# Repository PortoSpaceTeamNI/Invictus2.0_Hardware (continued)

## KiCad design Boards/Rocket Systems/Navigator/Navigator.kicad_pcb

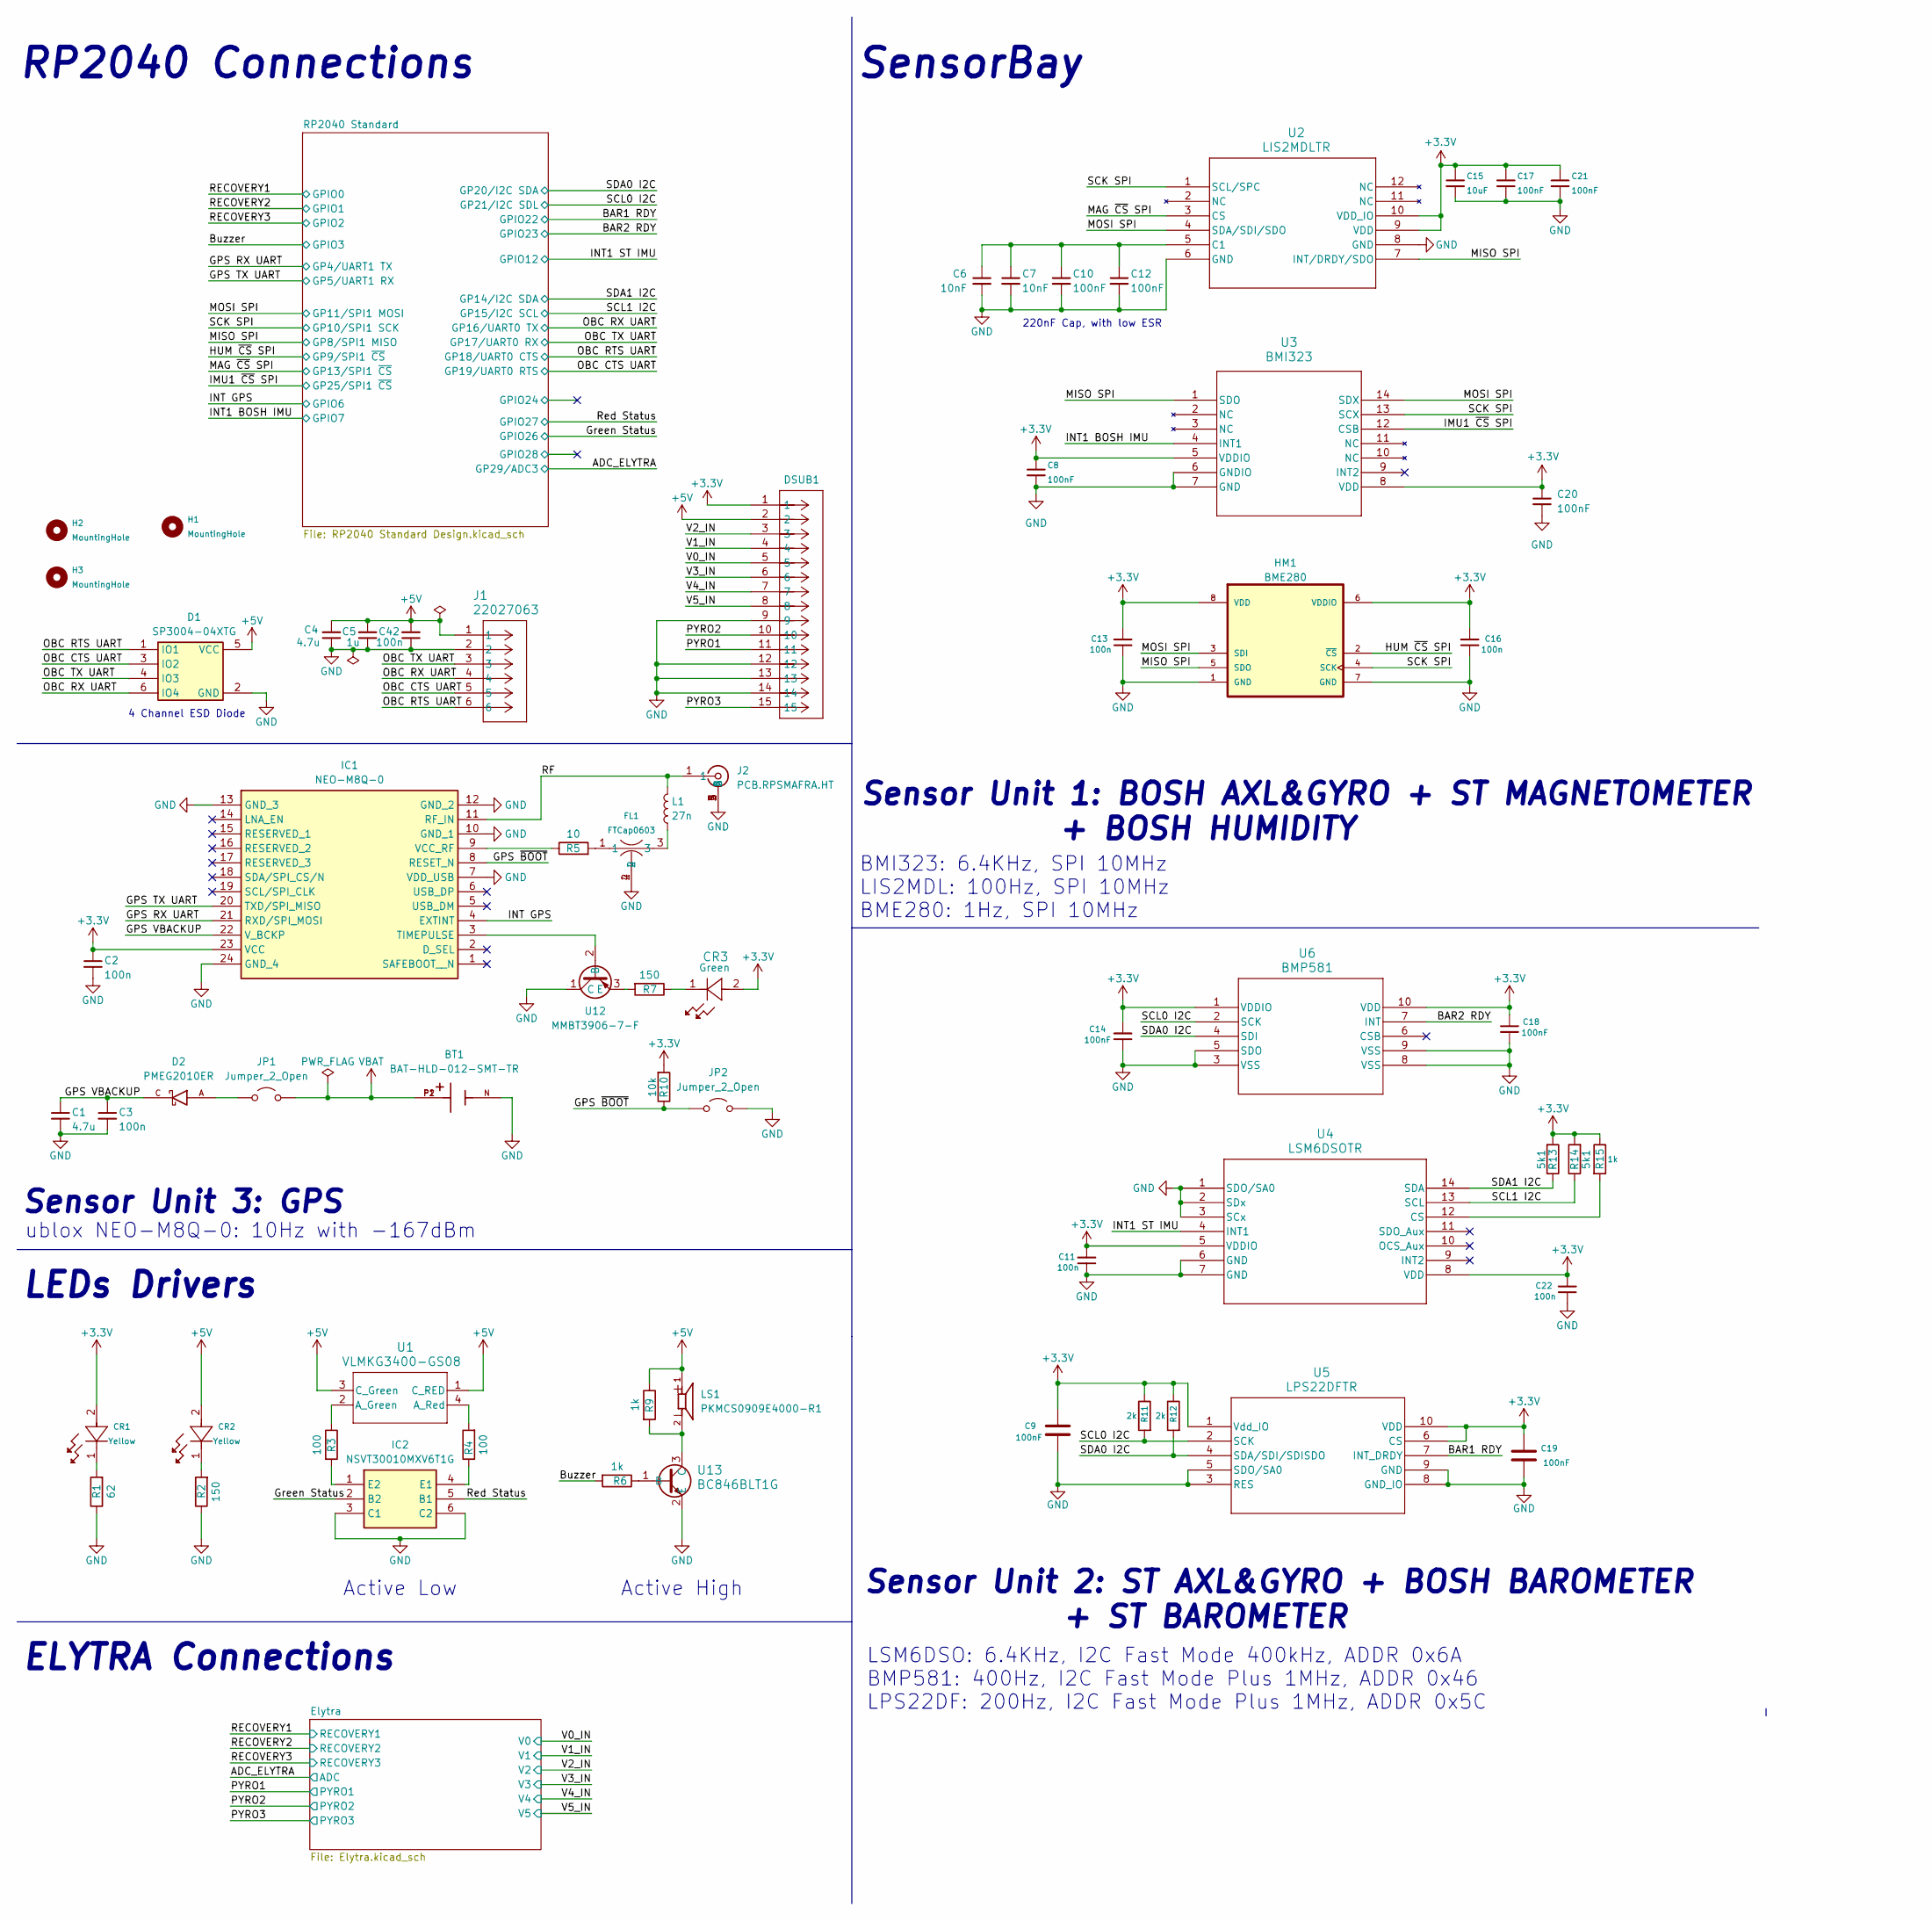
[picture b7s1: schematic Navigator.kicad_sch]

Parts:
BT1: BAT-HLD-012-SMT-TR; BAT_BAT-HLD-012-SMT-TR; PARTREV A
C1, C4: 4.7u; Capacitor_0402
C2, C3, C11, C13, C16, C22, C42: 100n; Capacitor_0402
C5: 1u; Capacitor_0402
C6, C7: 10nF; Capacitor_0402
C8, C9, C10, C12, C14, C17, C18, C19, C20, C21: 100nF; Capacitor_0402
C15: 10uF; Capacitor_0805
CR1, CR2: VLMY1300-GS08; LEDC1608X100N
CR3: VLMC3100-GS08; LED_PLCC_VSMB
D1: SP3004-04XTG; SOT563_LTF; Mouser Part Number 576-SP3004-04XTG
D2: PMEG2010ER; SODFL3517X110N; PARTREV 01
DSUB1: HDL15-SL-B
FL1: FTCap0603; FTCap_0603
H1, H2, H3: MountingHole; MountingHole_3.2mm_M3_ISO7380
HM1: BME280; Mouser Part Number 262-BME280
IC1: NEO-M8Q-0; NEO-M8_UBL; Mouser Part Number 377-NEO-M8Q-0
IC2: NSVT30010MXV6T1G; SOTFL50P160X60-6N; Mouser Part Number 863-NSVT30010MXV6T1G
J1: 22027063; CONN6X1_22027063_MOL
J2: PCB.RPSMAFRA.HT; PCBRPSMAFRAHT; Mouser Part Number 960-PCB.RPSMAFRA.HT
JP1, JP2: Jumper_2_Open; SolderJumper-2_P1.3mm_Open_RoundedPad1.0x1.5mm
L1: 27n; Inductor_0402
LS1: PKMCS0909E4000-R1; SPKR_PKMCS0909E4000-R1; PARTREV May 22, 2020
R1: 62; RES_0603
R2, R7: 150; RES_0603
R3, R4: 100; RES_0603
R5: 10; RES_0402
R6, R9: 1k; RES_0603
R10: 10k; RES_0402
R11, R12: 2k; RES_0402
R13, R14: 5k1; RES_0402
R15: 1k; RES_0402
U1: VLMKG3400-GS08; SMT_00-GS08_VIS
U2: LIS2MDLTR; LGA-12_2X2X1_STM
U3: BMI323; BMI323_BOS
U4: LSM6DSOTR; LGA-14L_2P5X3X0P86_STM
U5: LPS22DFTR; QFN_22DFTR_STM
U6: BMP581; QFN10_BMP581_BOS
U12: MMBT3906-7-F; SOT103P240X110-3N; MPN MMBT3906-7-F
U13: BC846BLT1G; SOT-23_ONS

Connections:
+3.3V: C2.1, C8.1, C9.2, C11.2, C13.2, C14.2, C15.1, C16.2, C17.1, C18.1, C19.2, C20.1, C21.1, C22.2, CR1.2, CR3.2, DSUB1.1, HM1.6 (VDDIO), HM1.8 (VDD), IC1.23 (VCC), R10.2, R11.1, R12.1, R13.2, R14.2, R15.1, U2.9 (VDD), U2.10 (VDD_IO), U3.5 (VDDIO), U3.8 (VDD), U4.5 (VDDIO), U4.8 (VDD), U5.1 (Vdd_IO), U5.6 (CS), U5.10 (VDD), U6.1 (VDDIO), U6.10 (VDD); also elsewhere on the board
+5V: C4.2, C5.2, C42.2, CR2.2, D1.5 (VCC), DSUB1.2, J1.1, LS1.1, R9.1, U1.1 (C_RED), U1.3 (C_Green); also elsewhere on the board
/BAR1 RDY: U5.7 (INT_DRDY); also elsewhere on the board
/BAR2 RDY: U6.7 (INT); also elsewhere on the board
/Buzzer: R6.2; also elsewhere on the board
/GPS RX UART: IC1.21 (RXD/SPI_MOSI); also elsewhere on the board
/GPS TX UART: IC1.20 (TXD/SPI_MISO); also elsewhere on the board
/GPS VBACKUP: C1.1, C3.1, D2.C, IC1.22 (V_BCKP)
/GPS ~BOOT: IC1.8 (RESET_N), JP2.1 (A), R10.1
/Green Status: IC2.2 (B2); also elsewhere on the board
/HUM ~CS SPI: HM1.2 (~CS); also elsewhere on the board
/IMU1 ~CS SPI: U3.12 (CSB); also elsewhere on the board
/INT1 BOSH IMU: U3.4 (INT1); also elsewhere on the board
/INT1 ST IMU: U4.4 (INT1); also elsewhere on the board
/INT GPS: IC1.4 (EXTINT); also elsewhere on the board
/MAG ~CS SPI: U2.3 (CS); also elsewhere on the board
/MISO SPI: HM1.5 (SDO), U2.7 (INT/DRDY/SDO), U3.1 (SDO); also elsewhere on the board
/MOSI SPI: HM1.3 (SDI), U2.4 (SDA/SDI/SDO), U3.14 (SDX); also elsewhere on the board
/OBC CTS UART: D1.3 (IO2), J1.5; also elsewhere on the board
/OBC RTS UART: D1.1 (IO1), J1.6; also elsewhere on the board
/OBC RX UART: D1.6 (IO4), J1.4; also elsewhere on the board
/OBC TX UART: D1.4 (IO3), J1.3; also elsewhere on the board
/PYRO1: DSUB1.11; also elsewhere on the board
/PYRO2: DSUB1.10; also elsewhere on the board
/PYRO3: DSUB1.15; also elsewhere on the board
/RF: IC1.11 (RF_IN), J2.1, L1.2
/Red Status: IC2.5 (B1); also elsewhere on the board
/SCK SPI: HM1.4 (SCK), U2.1 (SCL/SPC), U3.13 (SCX); also elsewhere on the board
/SCL0 I2C: R11.2, U5.2 (SCK), U6.2 (SCK); also elsewhere on the board
/SCL1 I2C: R14.1, U4.13 (SCL); also elsewhere on the board
/SDA0 I2C: R12.2, U5.4 (SDA/SDI/SDISDO), U6.4 (SDI); also elsewhere on the board
/SDA1 I2C: R13.1, U4.14 (SDA); also elsewhere on the board
/V0_IN: DSUB1.5; also elsewhere on the board
/V1_IN: DSUB1.4; also elsewhere on the board
/V2_IN: DSUB1.3; also elsewhere on the board
/V3_IN: DSUB1.6; also elsewhere on the board
/V4_IN: DSUB1.7; also elsewhere on the board
/V5_IN: DSUB1.8; also elsewhere on the board
GND: BT1.N, C1.2, C2.2, C3.2, C4.1, C5.1, C6.2, C7.2, C8.2, C9.1, C10.2, C11.1, C12.2, C13.1, C14.1, C15.2, C16.1, C17.2, C18.2, C19.1, C20.2, C21.2, C22.1, C42.1, D1.2 (GND), DSUB1.9, DSUB1.12, DSUB1.13, DSUB1.14, FL1.2, FL1.4, HM1.1 (GND), HM1.7 (GND), IC1.7 (VDD_USB), IC1.10 (GND_1), IC1.12 (GND_2), IC1.13 (GND_3), IC1.24 (GND_4), IC2.3 (C1), IC2.6 (C2), J1.2, J2.2, J2.3, J2.4, J2.5, JP2.2 (B), R1.1, R2.1, U2.6 (GND), U2.8 (GND), U3.6 (GNDIO), U3.7 (GND), U4.1 (SDO/SA0), U4.2 (SDx), U4.3 (SCx), U4.6 (GND), U4.7 (GND), U5.3 (RES), U5.5 (SDO/SA0), U5.8 (GND_IO), U5.9 (GND), U6.3 (VSS), U6.5 (SDO), U6.8 (VSS), U6.9 (VSS), U12.1 (C), U13.2 (E); also elsewhere on the board
unnamed: CR1.1, R1.2
unnamed: CR2.1, R2.2
unnamed: CR3.1, R7.1
unnamed: FL1.1, R5.2
unnamed: FL1.3, L1.1
unnamed: IC1.3 (TIMEPULSE), U12.2 (B)
unnamed: IC1.9 (VCC_RF), R5.1
unnamed: IC2.4 (E1), R4.1
unnamed: IC2.1 (E2), R3.2
unnamed: D2.A, JP1.1 (A)
unnamed: R3.1, U1.2 (A_Green)
unnamed: R4.2, U1.4 (A_Red)
unnamed: C6.1, C7.1, C10.1, C12.1, U2.5 (C1)
unnamed: R15.2, U4.12 (CS)
unnamed: R7.2, U12.3 (E)
unnamed: R6.1, U13.1 (B)
unnamed: LS1.2, R9.2, U13.3 (C)
VBAT: BT1.P1, BT1.P2, JP1.2 (B)

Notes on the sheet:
BMI323: 6.4KHz, SPI 10MHz LIS2MDL: 100Hz, SPI 10MHz BME280: 1Hz, SPI 10MHz
Sensor Unit 2: ST AXL&GYRO + BOSH BAROMETER + ST BAROMETER
SensorBay
Active Low
ELYTRA Connections
RP2040 Connections
Sensor Unit 3: GPS
Active High
LEDs Drivers
Sensor Unit 1: BOSH AXL&GYRO + ST MAGNETOMETER + BOSH HUMIDITY
4 Channel ESD Diode
ublox NEO-M8Q-0: 10Hz with -167dBm
LSM6DSO: 6.4KHz, I2C Fast Mode 400kHz, ADDR 0x6A BMP581: 400Hz, I2C Fast Mode Plus 1MHz, ADDR 0x46 LPS22DF: 200Hz, I2C Fast Mode Plus 1MHz, ADDR 0x5C
220nF Cap, with low ESR

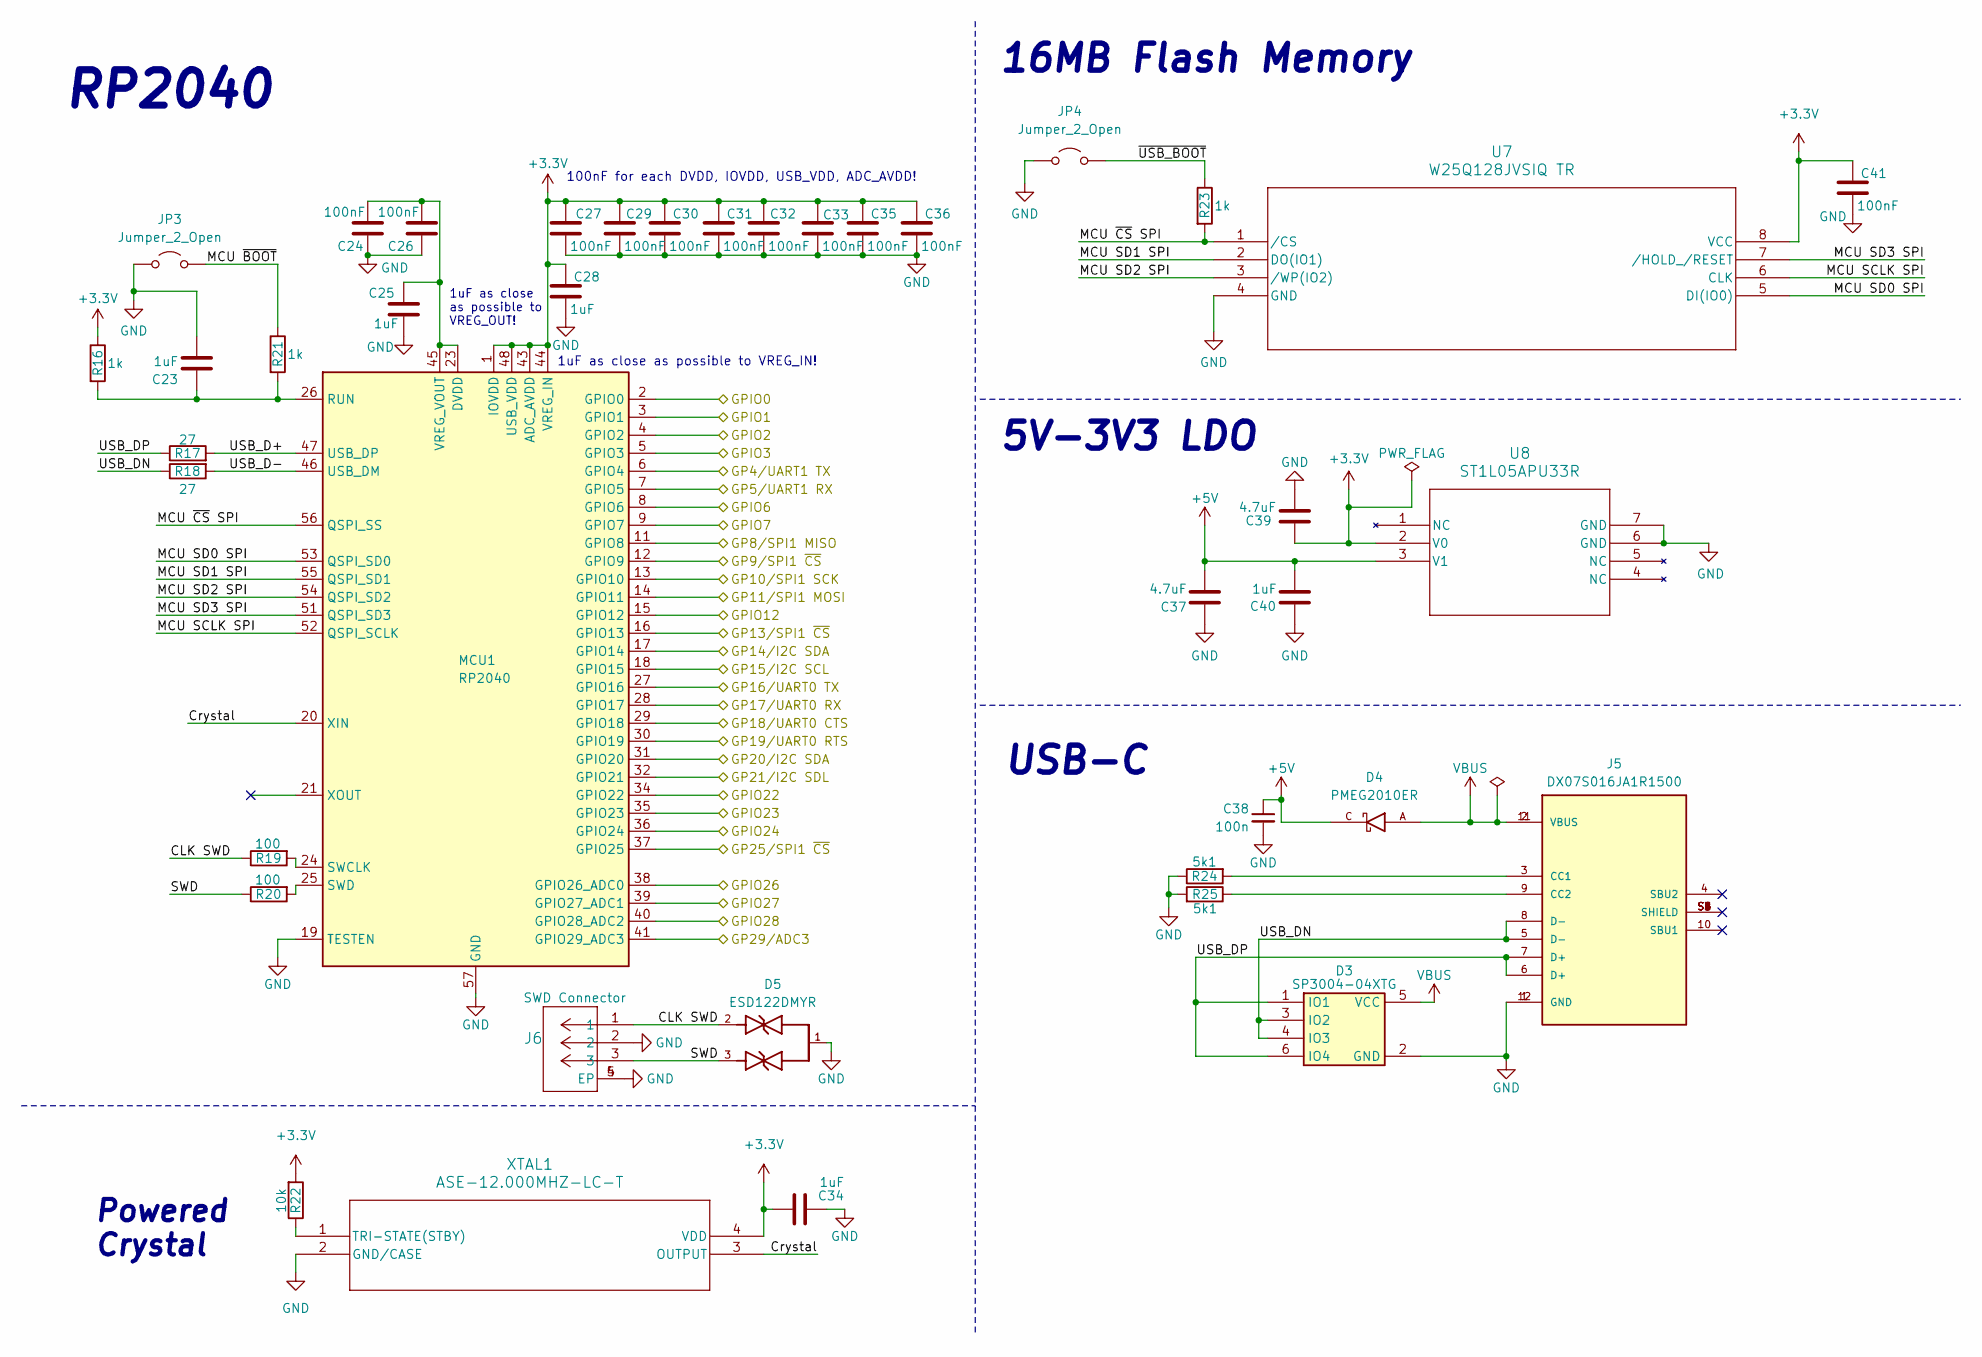
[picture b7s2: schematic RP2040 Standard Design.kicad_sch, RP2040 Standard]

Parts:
C23, C25, C28, C34, C40: 1uF; Capacitor_0402
C24, C26, C27, C29, C30, C31, C32, C33, C35, C36, C41: 100nF; Capacitor_0402
C37, C39: 4.7uF; Capacitor_0402
C38: 100n; Capacitor_0402
D3: SP3004-04XTG; SOT563_LTF; Mouser Part Number 576-SP3004-04XTG
D4: PMEG2010ER; SODFL3517X110N; PARTREV 01
D5: ESD122DMYR; DIO_ESD122DMYR; PARTREV A
J5: DX07S016JA1R1500; JAE_DX07S016JA1R1500; PARTREV 1
J6: BM03B-SRSS-TBLFSN; CONN_BM03B-SRSS-TBLFSN_JST
JP3, JP4: Jumper_2_Open; SolderJumper-2_P1.3mm_Open_RoundedPad1.0x1.5mm
MCU1: RP2040; QFN56_7X7_RPI
R16, R21, R23: 1k; RES_0402
R17, R18: 27; RES_0402
R19, R20: 100; RES_0402
R22: 10k; RES_0402
R24, R25: 5k1; RES_0402
U7: W25Q128JVSIQ TR; SOIC_208MIL_WIN
U8: ST1L05APU33R; DFN_5APU33R_STM
XTAL1: ASE-12.000MHZ-LC-T; ASE24576MHZLCT

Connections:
+3.3V: C27.1, C28.1, C29.1, C30.1, C31.1, C32.1, C33.1, C34.1, C35.1, C36.1, C39.2, C41.1, MCU1.1 (IOVDD), MCU1.10 (IOVDD), MCU1.22 (IOVDD), MCU1.33 (IOVDD), MCU1.42 (IOVDD), MCU1.43 (ADC_AVDD), MCU1.44 (VREG_IN), MCU1.48 (USB_VDD), MCU1.49 (IOVDD), R16.1, R22.2, U7.8 (VCC), U8.2 (V0), XTAL1.4 (VDD); also elsewhere on the board
+5V: C37.2, C38.1, C40.2, D4.C, U8.3 (V1); also elsewhere on the board
/ADC_ELYTRA: MCU1.41 (GPIO29_ADC3); also elsewhere on the board
/BAR1 RDY: MCU1.34 (GPIO22); also elsewhere on the board
/BAR2 RDY: MCU1.35 (GPIO23); also elsewhere on the board
/Buzzer: MCU1.5 (GPIO3); also elsewhere on the board
/GPS RX UART: MCU1.6 (GPIO4); also elsewhere on the board
/GPS TX UART: MCU1.7 (GPIO5); also elsewhere on the board
/Green Status: MCU1.38 (GPIO26_ADC0); also elsewhere on the board
/HUM ~CS SPI: MCU1.12 (GPIO9); also elsewhere on the board
/IMU1 ~CS SPI: MCU1.37 (GPIO25); also elsewhere on the board
/INT1 BOSH IMU: MCU1.9 (GPIO7); also elsewhere on the board
/INT1 ST IMU: MCU1.15 (GPIO12); also elsewhere on the board
/INT GPS: MCU1.8 (GPIO6); also elsewhere on the board
/MAG ~CS SPI: MCU1.16 (GPIO13); also elsewhere on the board
/MISO SPI: MCU1.11 (GPIO8); also elsewhere on the board
/MOSI SPI: MCU1.14 (GPIO11); also elsewhere on the board
/OBC CTS UART: MCU1.30 (GPIO19); also elsewhere on the board
/OBC RTS UART: MCU1.29 (GPIO18); also elsewhere on the board
/OBC RX UART: MCU1.27 (GPIO16); also elsewhere on the board
/OBC TX UART: MCU1.28 (GPIO17); also elsewhere on the board
/RECOVERY1: MCU1.2 (GPIO0); also elsewhere on the board
/RECOVERY2: MCU1.3 (GPIO1); also elsewhere on the board
/RECOVERY3: MCU1.4 (GPIO2); also elsewhere on the board
/RP2040 Standard/CLK SWD: D5.2, J6.1, R19.1
/RP2040 Standard/Crystal: MCU1.20 (XIN), XTAL1.3 (OUTPUT)
/RP2040 Standard/GPIO24: MCU1.36 (GPIO24)
/RP2040 Standard/GPIO28: MCU1.40 (GPIO28_ADC2)
/RP2040 Standard/MCU SCLK SPI: MCU1.52 (QSPI_SCLK), U7.6 (CLK)
/RP2040 Standard/MCU SD0 SPI: MCU1.53 (QSPI_SD0), U7.5 (DI(IO0))
/RP2040 Standard/MCU SD1 SPI: MCU1.55 (QSPI_SD1), U7.2 (DO(IO1))
/RP2040 Standard/MCU SD2 SPI: MCU1.54 (QSPI_SD2), U7.3 (/WP(IO2))
/RP2040 Standard/MCU SD3 SPI: MCU1.51 (QSPI_SD3), U7.7 (/HOLD_/RESET)
/RP2040 Standard/MCU ~BOOT: JP3.2 (B), R21.1
/RP2040 Standard/MCU ~CS SPI: MCU1.56 (QSPI_SS), R23.2, U7.1 (/CS)
/RP2040 Standard/SWD: D5.3, J6.3, R20.1
/RP2040 Standard/USB_D+: MCU1.47 (USB_DP), R17.2
/RP2040 Standard/USB_D-: MCU1.46 (USB_DM), R18.2
/RP2040 Standard/USB_DN: D3.3 (IO2), D3.4 (IO3), J5.5 (D-), J5.8 (D-), R18.1
/RP2040 Standard/USB_DP: D3.1 (IO1), D3.6 (IO4), J5.6 (D+), J5.7 (D+), R17.1
/RP2040 Standard/~USB_BOOT: JP4.2 (B), R23.1
/Red Status: MCU1.39 (GPIO27_ADC1); also elsewhere on the board
/SCK SPI: MCU1.13 (GPIO10); also elsewhere on the board
/SCL0 I2C: MCU1.32 (GPIO21); also elsewhere on the board
/SCL1 I2C: MCU1.18 (GPIO15); also elsewhere on the board
/SDA0 I2C: MCU1.31 (GPIO20); also elsewhere on the board
/SDA1 I2C: MCU1.17 (GPIO14); also elsewhere on the board
GND: C23.2, C24.1, C25.2, C26.1, C27.2, C28.2, C29.2, C30.2, C31.2, C32.2, C33.2, C34.2, C35.2, C36.2, C37.1, C38.2, C39.1, C40.1, C41.2, D3.2 (GND), D5.1, J5.1 (GND), J5.12 (GND), J6.2, J6.4 (EP), J6.5 (EP), JP3.1 (A), JP4.1 (A), MCU1.19 (TESTEN), MCU1.57 (GND), R24.1, R25.2, U7.4 (GND), U8.6 (GND), U8.7 (GND), XTAL1.2 (GND/CASE); also elsewhere on the board
unnamed: J5.3 (CC1), R24.2
unnamed: J5.9 (CC2), R25.1
unnamed: C23.1, MCU1.26 (RUN), R16.2, R21.2
unnamed: MCU1.24 (SWCLK), R19.2
unnamed: MCU1.25 (SWD), R20.2
unnamed: C24.2, C25.1, C26.2, MCU1.23 (DVDD), MCU1.45 (VREG_VOUT), MCU1.50 (DVDD)
unnamed: R22.1, XTAL1.1 (TRI-STATE(STBY))
VBUS: D3.5 (VCC), D4.A, J5.2 (VBUS), J5.11 (VBUS)

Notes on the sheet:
1uF as close as possible to VREG_OUT!
Powered Crystal
RP2040
5V-3V3 LDO
16MB Flash Memory
1uF as close as possible to VREG_IN!
100nF for each DVDD, IOVDD, USB_VDD, ADC_AVDD!
USB-C

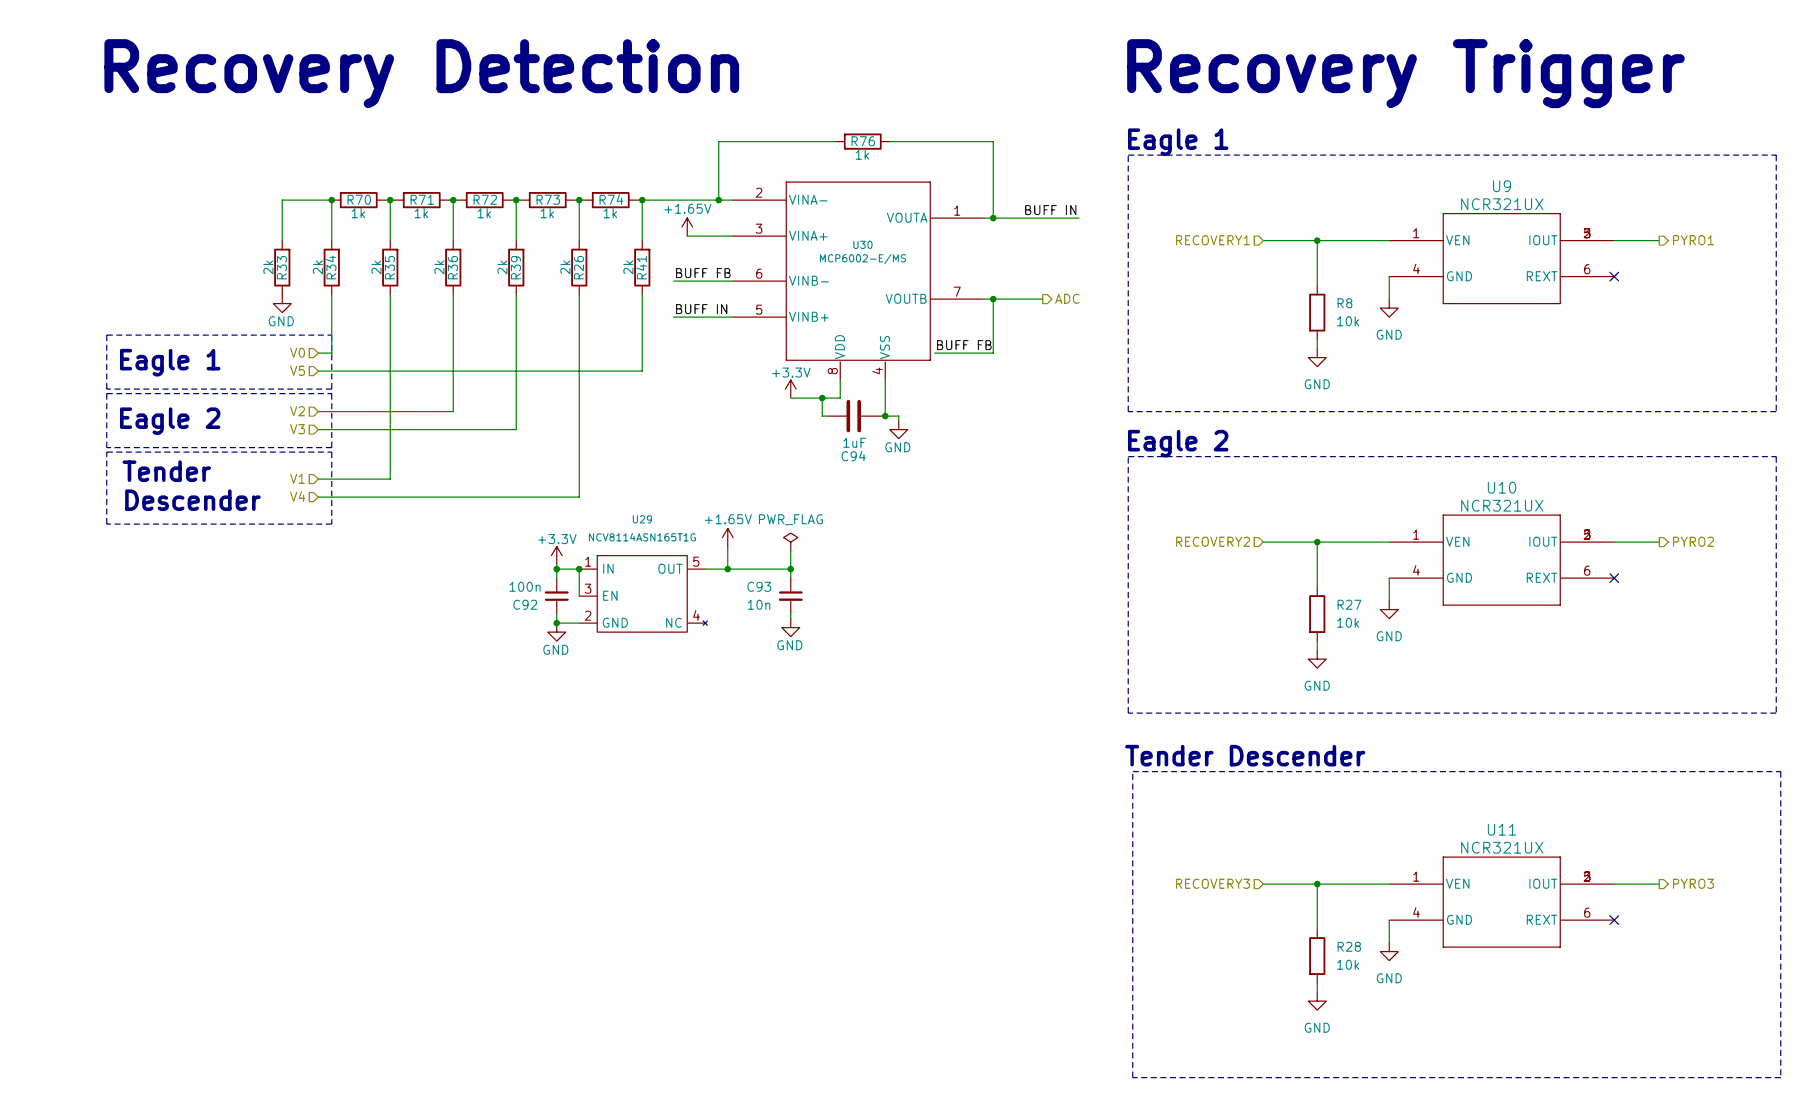
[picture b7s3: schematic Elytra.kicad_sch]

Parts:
C92: 100n; Capacitor_0402
C93: 10n; Capacitor_0402
C94: 1uF; Capacitor_0402
R8, R27, R28: 10k; RES_0402
R26, R33, R34, R35, R36, R39, R41: 2k; RES_0603
R70, R71, R72, R73, R74: 1k; RES_0603
R76: 1k; RES_0402
U9, U10, U11: NCR321UX; TSOP6_SOT457_NEX
U29: NCV8114ASN165T1G; SOT95P275X120-5N
U30: MCP6002-E/MS; MSOP8_MC_MCH

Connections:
+1.65V: C93.1, U29.5 (OUT), U30.3 (VINA+)
+3.3V: C92.2, C94.1, U29.1 (IN), U29.3 (EN), U30.8 (VDD); also elsewhere on the board
/ADC_ELYTRA: U30.6 (VINB-), U30.7 (VOUTB); also elsewhere on the board
/Elytra/BUFF IN: R76.1, U30.1 (VOUTA), U30.5 (VINB+)
/PYRO1: U9.2 (IOUT), U9.3 (IOUT), U9.5 (IOUT); also elsewhere on the board
/PYRO2: U10.2 (IOUT), U10.3 (IOUT), U10.5 (IOUT); also elsewhere on the board
/PYRO3: U11.2 (IOUT), U11.3 (IOUT), U11.5 (IOUT); also elsewhere on the board
/RECOVERY1: R8.1, U9.1 (VEN); also elsewhere on the board
/RECOVERY2: R27.1, U10.1 (VEN); also elsewhere on the board
/RECOVERY3: R28.1, U11.1 (VEN); also elsewhere on the board
/V0_IN: R34.1; also elsewhere on the board
/V1_IN: R35.1; also elsewhere on the board
/V2_IN: R36.1; also elsewhere on the board
/V3_IN: R39.1; also elsewhere on the board
/V4_IN: R26.1; also elsewhere on the board
/V5_IN: R41.1; also elsewhere on the board
GND: C92.1, C93.2, C94.2, R8.2, R27.2, R28.2, R33.1, U9.4 (GND), U10.4 (GND), U11.4 (GND), U29.2 (GND), U30.4 (VSS); also elsewhere on the board
unnamed: R26.2, R73.1, R74.2
unnamed: R33.2, R34.2, R70.2
unnamed: R35.2, R70.1, R71.2
unnamed: R36.2, R71.1, R72.2
unnamed: R39.2, R72.1, R73.2
unnamed: R41.2, R74.1, R76.2, U30.2 (VINA-)

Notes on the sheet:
Recovery Trigger
Recovery Detection
Tender Descender
Tender Descender
Eagle 2
Eagle 1

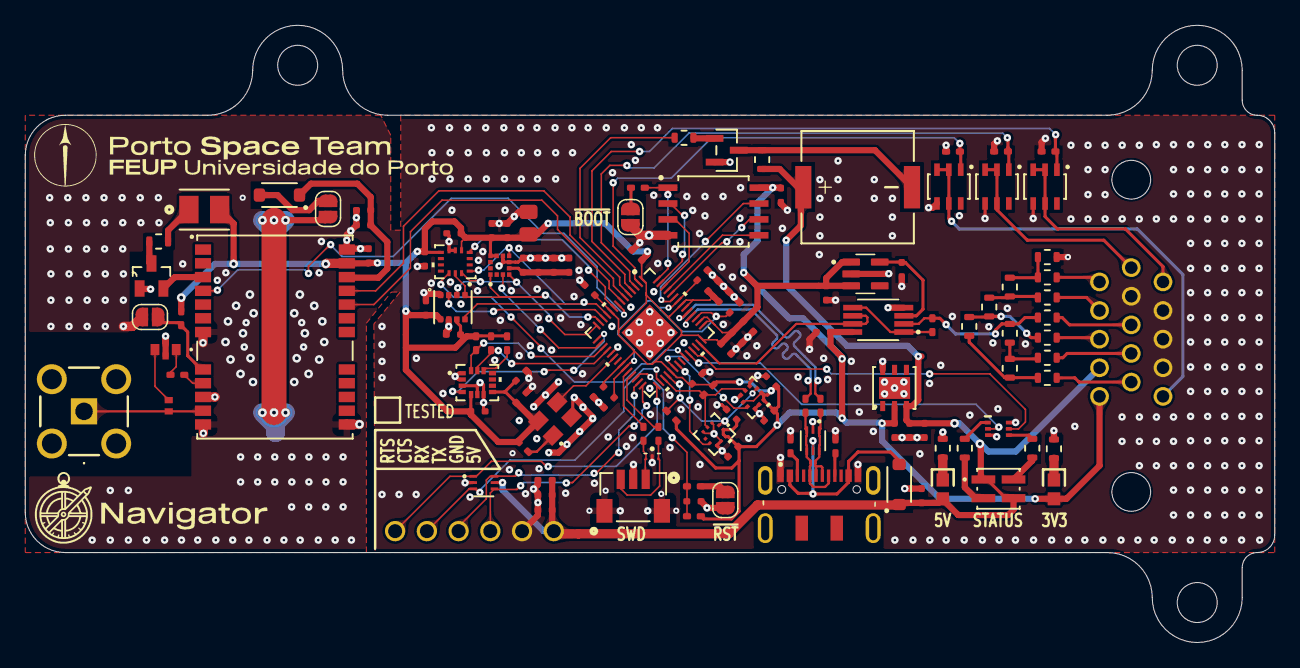
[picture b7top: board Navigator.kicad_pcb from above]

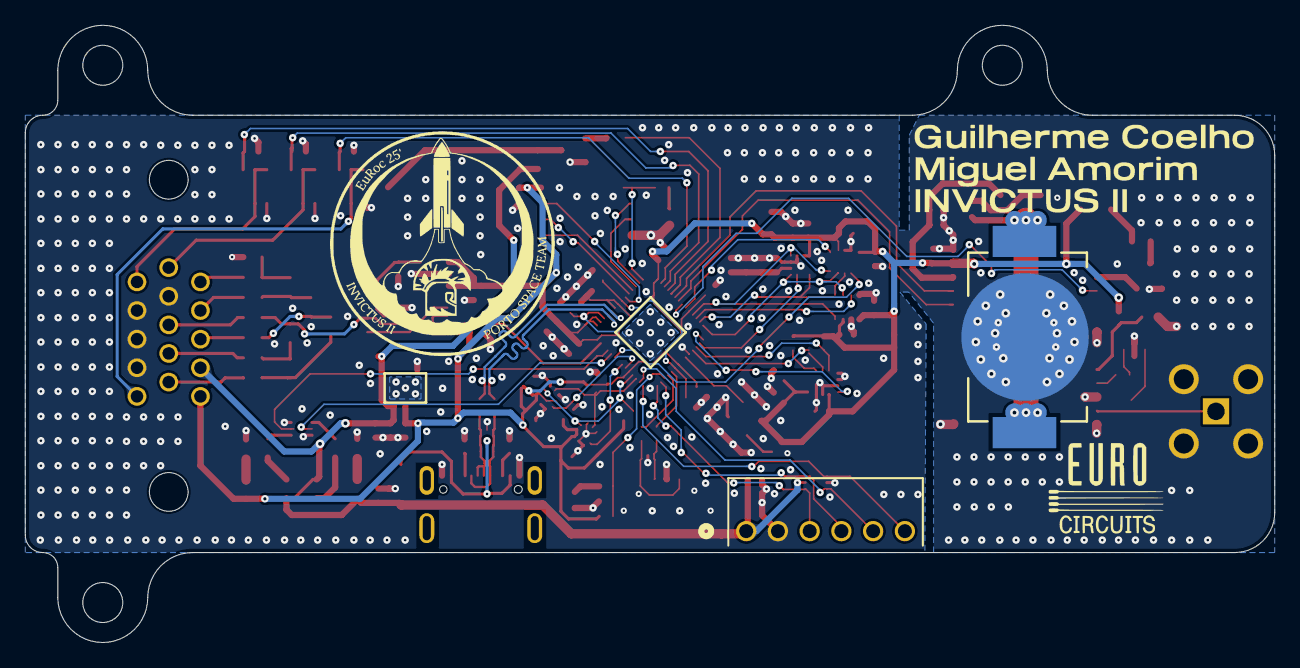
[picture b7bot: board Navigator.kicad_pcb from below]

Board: 4 copper layers, 100.0 x 49.4 mm, 129 parts (2 on the bottom side), 92 nets.

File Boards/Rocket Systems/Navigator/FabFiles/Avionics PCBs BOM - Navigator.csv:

On Board Computer,,,,,,
Qty,Value,Parts,Device,Package,Description,Mouser Electronics
2,VLMY1300-GS08,"CR1, CR2",VLMY1300-GS08,LEDC1608X100N,Yellow LED,78-VLMY1300-GS08
1,VLMC3100-GS08,CR3,VLMC3100-GS08,LED_PLCC_VSMB,BiColor Red Green LED,78-VLMC3100
2,SP3004-04XTG,"D1, D3",SP3004-04XTG,SOT563_LTF,ESD/TVS protection Diode,576-SP3004-04XTG
2,PMEG2010ER,"D2, D4",PMEG2010ER,SODFL3517X110N,Schottky Diode,771-PMEG2010ER115
1,ESD122DMYR,D5,ESD122DMYR,DIO_ESD122DMYR,ESD/TVS protection Diode,595-ESD122DMYR
1,NFM18CC471R1C3D,FL1,NFM18CC471R1C3D,FTCap_0603,Feed Through Capacitor,81-NFM18CC471R1C3D
1,BME280,HM1,BME280,PSON65P250X250X100-8N,Humidity sensor,262-BME280
1,NEO-M8Q-0,IC1,NEO-M8Q-0,NEO-M8_UBL,GPS,377-NEO-M8Q-0
1,NSVT30010MXV6T1G,IC2,NSVT30010MXV6T1G,SOT-563_1P3X1P7_ONS,Dual PNP transistor,863-NSVT30010MXV6T1G
1,BC846BLT1G,IC3,BC846BLT1G,SOT96P237X111-3N,NPN BJT Transistor,863-BC846BLT1G
1,LMV321LILT,IC4,LMV321LILT,SOT95P280X145-5N,Operational Amplifier,511-LMV321LILT
1,PKMCS0909E4000-R1,LS1,PKMCS0909E4000-R1,SPKR_PKMCS0909E4000-R1,Buzzer,81-PKMCS0909E4000-R1
1,SC0914(13),MCU1,SC0914(13),QFN56_7X7_RPI,RP2040,358-SC091413 
1, MMBT3906-7-F,Q1, MMBT3906-7-F,SOT-23-3,PNP Transistor ,621-MMBT3906-F
1,VLMKG3400-GS08,U1,VLMKG3400-GS08,SMT_00-GS08_VIS,Timer GPS MOSFET,78-VLMKG3400-GS08
1,LIS2MDLTR,U2,LIS2MDLTR,LGA-12_2X2X1_STM,Magnetometer Sensor,511-LIS2MDLTR
1,BMI323,U3,BMI323,BMI323_BOS,IMU,262-BMI323
1,LSM6DSOTR,U4,LSM6DSOTR,LGA-14L_2P5X3X0P86_STM,IMU,511-LSM6DSOTR
1,LPS22DFTR,U5,LPS22DFTR,QFN_22DFTR_STM,Barometer,511-LPS22DFTR
1,BMP581,U6,BMP581,QFN10_BMP581_BOS,Barometer,262-BMP581
1,W25Q128JVSIQ TR,U7,W25Q128JVSIQ TR,SOIC_208MIL_WIN,Flash Drive,454-W25Q128JVSIQTR
1,ST1L05APU33R,U8,ST1L05APU33R,DFN_5APU33R_STM,ST Voltage Regulator LDO 5V to 3.3V,511-ST1L05APU33R
3,NCR321UX,"U9, U10, U11",NCR321UX,TSOP6_SOT457_NEX,LED drivers,771-NCR321UX
1,ASE-12.000MHZ-LC-T,XTAL1,ASE-12.000MHZ-LC-T,ASE24576MHZLCT,Clock Oscilator,815-ASE-12.000MLCT
30,100n,"C2, C3, C8, C9, C10, C11, C12, C13, C14, C16, C17, C18, C19, C20, C21, C22, C24, C26, C27, C29, C30, C31, C32, C33, C35, C36, C38, C41, C42, C43",GPC0402104-16,C0402,CAPACITOR,
6,1uF,"C5, C23, C25, C28, C34, C40",GPC0402105-16,C0402,CAPACITOR,
4,4.7u,"C1, C4, C37, C39",GPC0402475-6.3,C0402,CAPACITOR,
2,10nF,"C6, C7",GPC0402103-25,C0402,CAPACITOR,
1,10uF,C15,GPC0805103,C0805,CAPACITOR,
5,10k,"R8, R10, R22, R30, R40",GPR040210K,R0402,RESISTOR,
4,5k1,"R13, R14, R24, R25",GPR04025K1,R0402,RESISTOR,
4,1k,"R15, R16, R21, R23",GPR04021K,R0402,RESISTOR,
3,1K,"R6, R9, R37",GPR06031K,R0603,RESISTOR,
3,100K,"R26, R36, R39",GPR0603100K,R0603,RESISTOR,
2,150,"R2, R7",GPR0603150R,R0603,RESISTOR,
2,100,"R3, R4",GPR0603100R,R0603,RESISTOR,
2,2k,"R11, R12",GPR04022K,R0402,RESISTOR,
2,27,"R17, R18",GPR040227R,R0402,RESISTOR,
2,100,"R19, R20",GPR0402100R,R0402,RESISTOR,
1,62,R1,GPR060362R,R0603,RESISTOR,
1,10,R5,GPR040210R,R0402,RESISTOR,
1,2.7K,R27,GPR04022K7,R0402,RESISTOR,
1,750,R28,GPR0805750R,R0805,RESISTOR,
1,22K,R29,GPR040222K,R0402,RESISTOR,
1,51,R31,GPR060351R,R0603,RESISTOR,
1,6.2K,R32,GPR06036K2,R0603,RESISTOR,
1,200K,R33,GPR0603200K,R0603,RESISTOR,
1,1.5k,R34,GPR06031K5,R0603,RESISTOR,
1,11K,R35,GPR060311K,R0603,RESISTOR,
1,24K,R38,GPR060324K,R0603,RESISTOR,
1,1.3K,R41,GPR04021K3,R0402,RESISTOR,
1,24K,R42,GPR040224K,R0402,RESISTOR,
1,27n,L1,LQW15AN27NJ8ZD ,Inductor0402,INDUCTOR,81-LQW15AN27NJ8ZD
1,BAT-HLD-012-SMT-TR,BT1,BAT_BAT-HLD-012-SMT-TR,BAT_BAT-HLD-012-SMT-TR,Battery holder,712-BAT-HLD012SMT-TR
1,22027063,J1,CONN6X1_22027063_MOL,CONN6X1_22027063_MOL,6 Position Connector,538-22-02-7063 
1,PCB.RPSMAFRA.HT,J2,PCBRPSMAFRAHT,PCBRPSMAFRAHT,RP-SMA Jack connector,PCB.RPSMAFRA.HT 
1,DX07S016JA1R1500,J5,JAE_DX07S016JA1R1500,JAE_DX07S016JA1R1500,USB connector,656-DX07S016JA1R1500 
1,BM03B-SRSS-TBLFSN,J6,CONN_BM03B-SRSS-TBLFSN_JST,CONN_BM03B-SRSS-TBLFSN_JST,SWD Connector,306-BM03BSRSSTBLFSNP 
1,HDL15-SL-B,DSUB1,HDL15-SL-B,HDL15-SL-B,VGA connector,
